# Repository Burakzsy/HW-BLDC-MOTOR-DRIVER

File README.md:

## BLDC Motor Sürücüsü Tasarımı

STP75NF75 Mosfet ve IR2104 mosfet sürücüsü kullanılmıştır.

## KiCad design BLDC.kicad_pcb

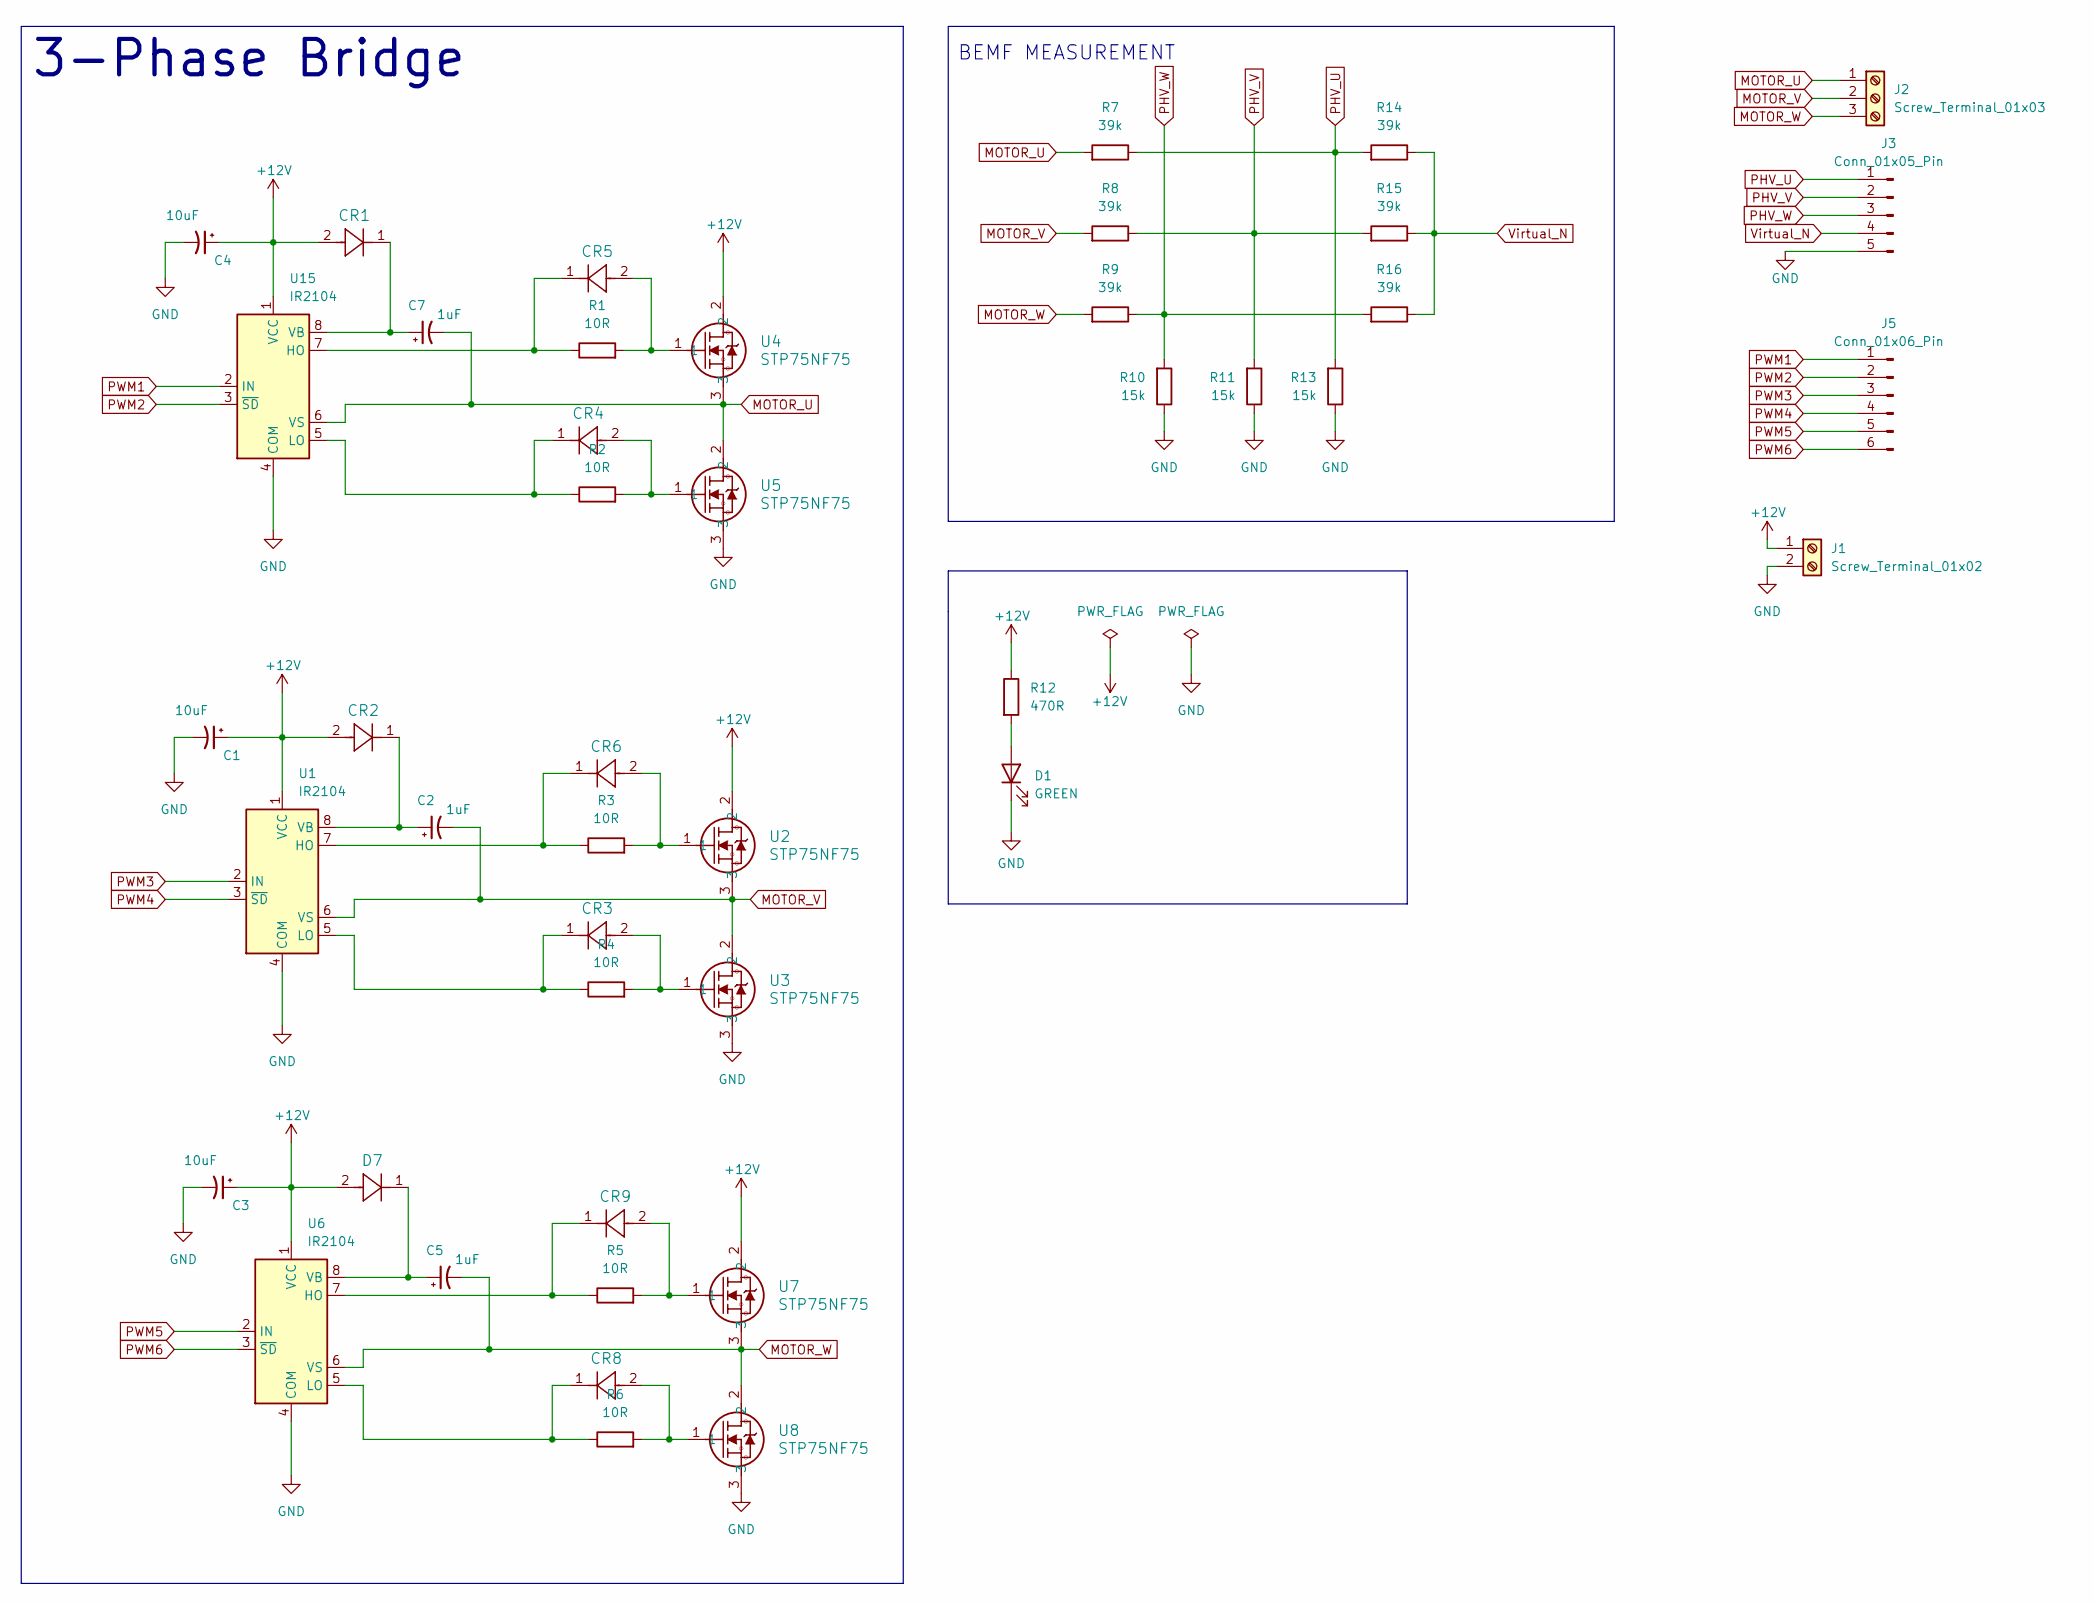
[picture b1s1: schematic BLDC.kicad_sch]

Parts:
C1, C3, C4: 10uF; CP_Radial_D4.0mm_P1.50mm
C2, C5, C7: 1uF; CP_Radial_D5.0mm_P2.00mm
CR1, CR2, CR3, CR4, CR5, CR6, CR8, CR9: UF4007-E3/54; DO-204AL
D1: GREEN; LED_D5.0mm
D7: UF4007-E3/54; DO-204AL
J1: Screw_Terminal_01x02; TerminalBlock_MetzConnect_Type011_RT05502HBWC_1x02_P5.00mm_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
J2: Screw_Terminal_01x03; TerminalBlock_MetzConnect_Type011_RT05503HBWC_1x03_P5.00mm_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
J3: Conn_01x05_Pin; PinHeader_1x05_P2.54mm_Vertical
J5: Conn_01x06_Pin; PinHeader_1x06_P2.54mm_Vertical
R1, R2, R3, R4, R5, R6: 10R; R_Axial_DIN0207_L6.3mm_D2.5mm_P7.62mm_Horizontal
R7, R8, R9, R14, R15, R16: 39k; R_Axial_DIN0207_L6.3mm_D2.5mm_P7.62mm_Horizontal
R10, R11, R13: 15k; R_Axial_DIN0207_L6.3mm_D2.5mm_P7.62mm_Horizontal
R12: 470R; R_Axial_DIN0207_L6.3mm_D2.5mm_P7.62mm_Horizontal
U1, U6, U15: IR2104; DIP-8_W7.62mm_LongPads
U2, U3, U4, U5, U7, U8: STP75NF75; TO-220_STM

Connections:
+12V: C1.1, C3.1, C4.1, CR1.2, CR2.2, D7.2, J1.1, R12.1, U1.1 (VCC), U2.2, U4.2, U6.1 (VCC), U7.2, U15.1 (VCC); also elsewhere on the board
GND: C1.2, C3.2, C4.2, D1.1 (K), J1.2, J3.5, R10.1, R11.1, R13.1, U1.4 (COM), U3.3, U5.3, U6.4 (COM), U8.3, U15.4 (COM)
MOTOR_U: C7.2, J2.1, R7.2, U4.3, U5.2, U15.6 (VS)
MOTOR_V: C2.2, J2.2, R8.2, U1.6 (VS), U2.3, U3.2
MOTOR_W: C5.2, J2.3, R9.2, U6.6 (VS), U7.3, U8.2
unnamed: CR3.2, R4.2, U3.1
unnamed: CR4.2, R2.2, U5.1
unnamed: CR5.2, R1.2, U4.1
unnamed: CR6.2, R3.2, U2.1
unnamed: CR8.2, R6.2, U8.1
unnamed: CR9.2, R5.2, U7.1
unnamed: D1.2 (A), R12.2
unnamed: CR6.1, R3.1, U1.7 (HO)
unnamed: CR3.1, R4.1, U1.5 (LO)
unnamed: C2.1, CR2.1, U1.8 (VB)
unnamed: CR9.1, R5.1, U6.7 (HO)
unnamed: CR8.1, R6.1, U6.5 (LO)
unnamed 17: C5.1, D7.1, U6.8 (VB); also elsewhere on the board
unnamed: CR5.1, R1.1, U15.7 (HO)
unnamed: CR4.1, R2.1, U15.5 (LO)
unnamed: C7.1, CR1.1, U15.8 (VB)
PHV_U: J3.1, R7.1, R13.2, R14.2
PHV_V: J3.2, R8.1, R11.2, R15.2
PHV_W: J3.3, R9.1, R10.2, R16.2
PWM1: J5.1, U15.2 (IN)
PWM2: J5.2, U15.3 (~SD)
PWM3: J5.3, U1.2 (IN)
PWM4: J5.4, U1.3 (~SD)
PWM5: J5.5, U6.2 (IN)
PWM6: J5.6, U6.3 (~SD)
Virtual_N: J3.4, R14.1, R15.1, R16.1

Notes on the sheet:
BEMF MEASUREMENT
3-Phase Bridge

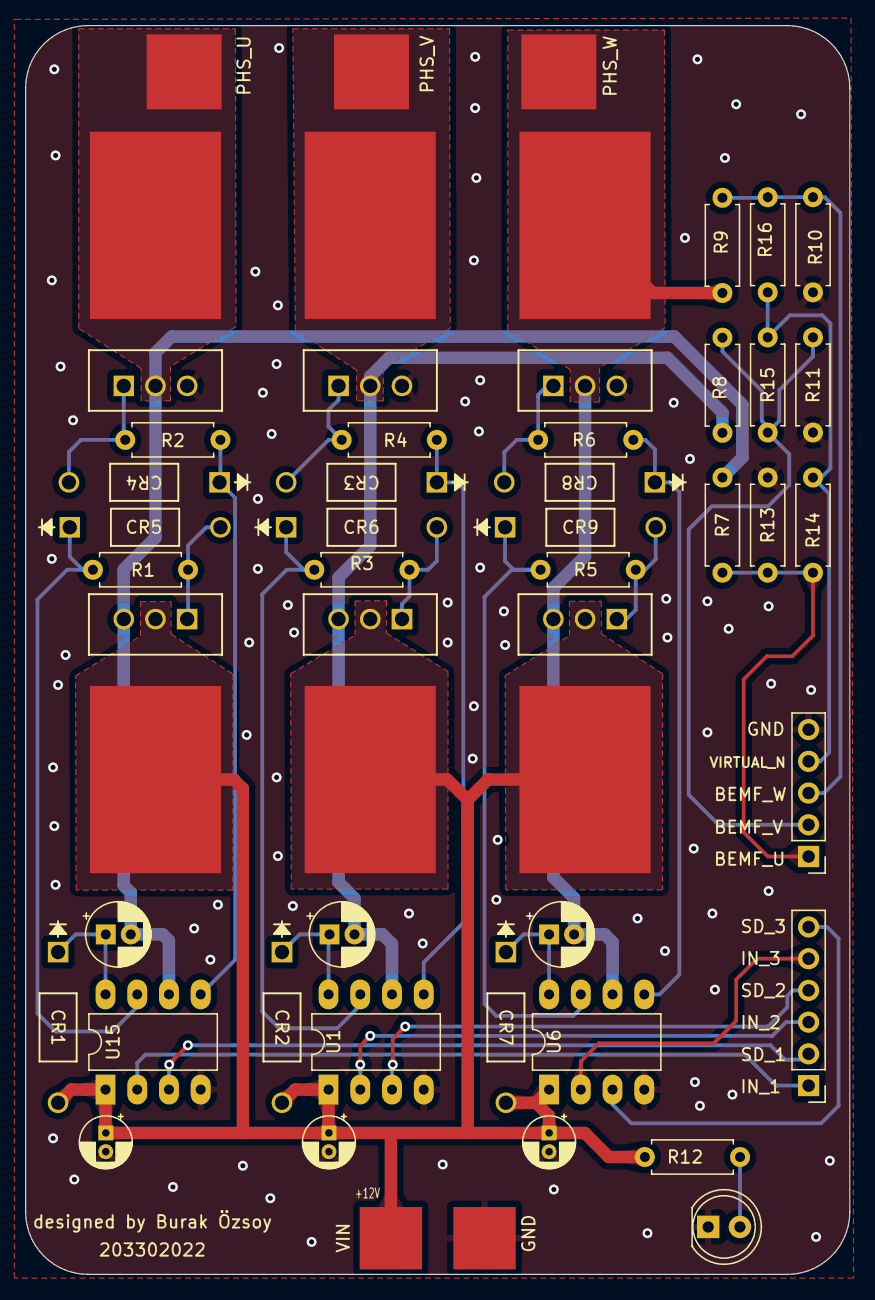
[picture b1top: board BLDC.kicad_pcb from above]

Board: 2 copper layers, 66.0 x 100.0 mm, 45 parts (0 on the bottom side), 31 nets.

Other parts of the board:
CR7: UF4007-E3/54; DO-204AL

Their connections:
+12V: CR7.2; also elsewhere on the board
unnamed 17: CR7.1; also elsewhere on the board
